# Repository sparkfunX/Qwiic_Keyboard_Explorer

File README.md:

Qwiic_Keyboard_Explorer
========================================

[*Qwiic Keyboard Explorer*](https://www.sparkfun.com/products/16184)

The Qwiic Keyboard Explorer is a 14-key mechanical keyboard kit based on our Qwiic Pro Micro development board. On its own, it makes a conveniently sized programmable macro pad, but we've also included plenty of prototyping space along the top for experimenting with all kinds of keyboard peripherals. If soldering isn't your thing, take advantage of the Pro Micro's Qwiic connector to attach any board from our Qwiic ecosystem! The standoff holes surrounding the prototyping area are spaced to accommodate most Qwiic boards for convenient mounting.

SparkFun labored with love to design this board. Feel like supporting open source hardware? 
Buy a [board](https://www.sparkfun.com/products/16184) from SparkFun!

Repository Contents
-------------------

* **/Hardware** - Eagle design files (.brd, .sch)
* **/Software** - Arduino Example Code

License Information
-------------------

This product is _**open source**_! 

Please review the LICENSE.md file for license information. 

If you have any questions or concerns on licensing, please contact technical support on our [SparkFun forums](https://forum.sparkfun.com/viewforum.php?f=152).

Distributed as-is; no warranty is given.

- Your friends at SparkFun.

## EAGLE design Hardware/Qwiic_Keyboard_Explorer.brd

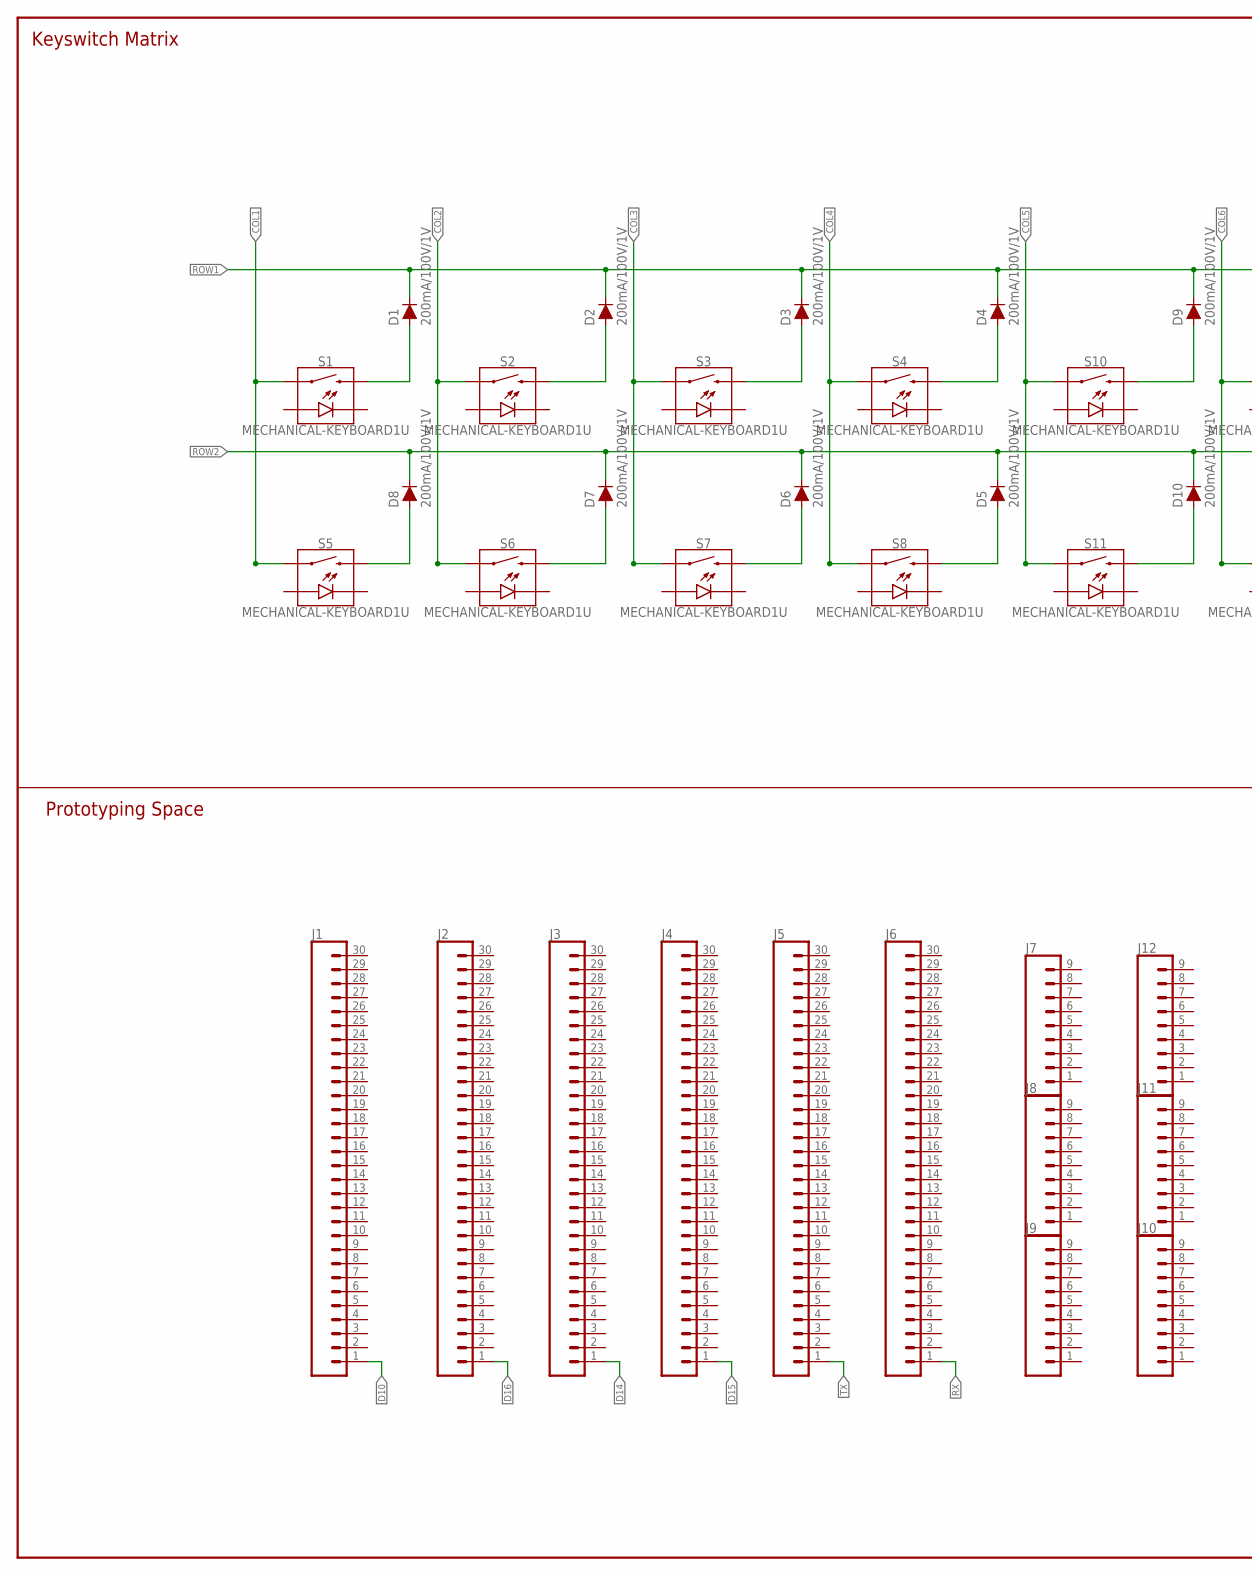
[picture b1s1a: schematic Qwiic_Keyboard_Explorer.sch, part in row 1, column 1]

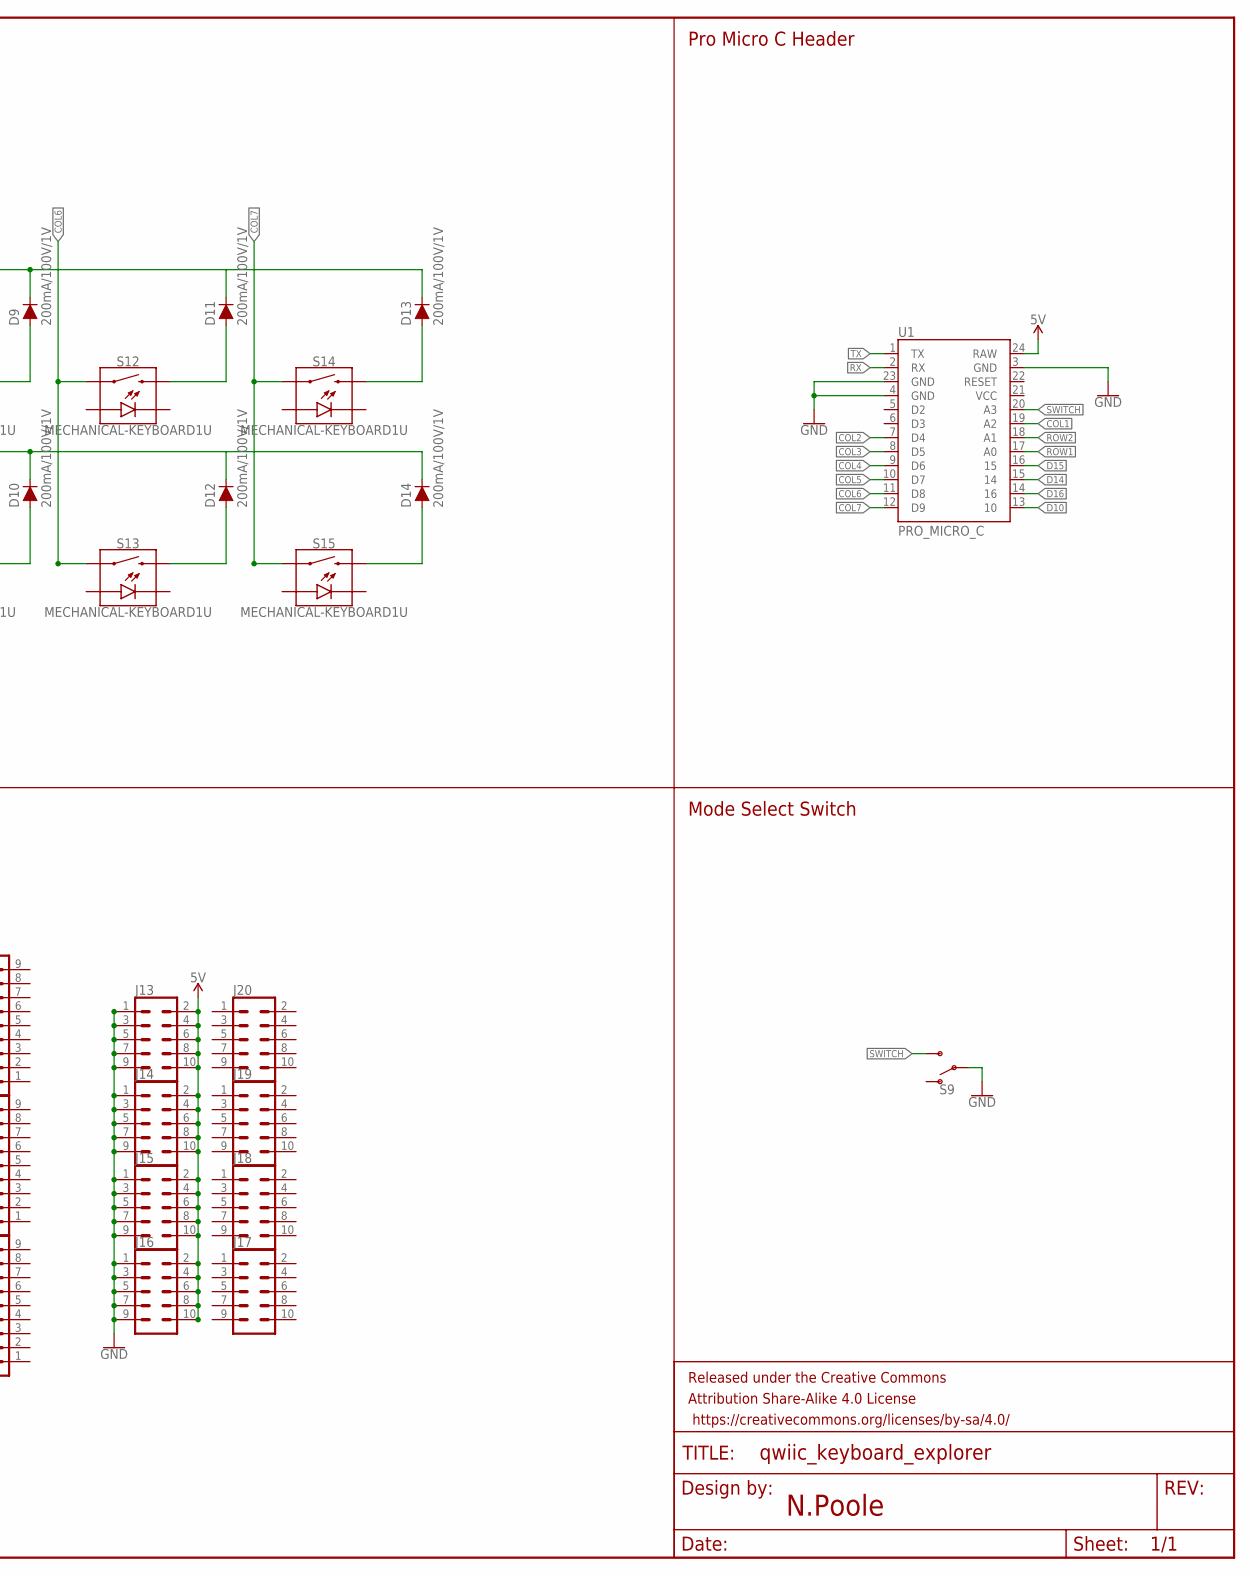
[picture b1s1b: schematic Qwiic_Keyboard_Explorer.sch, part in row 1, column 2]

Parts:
D1, D2, D3, D4, D5, D6, D7, D8, D9, D10, D11, D12, D13, D14: 200mA/100V/1V; DIODE-1N4148-KIT
FRAME1: FRAME-LEDGER; CREATIVE_COMMONS
J1, J2, J3, J4, J5, J6: CONN_30NO_SILK; 1X30_NO_SILK
J7, J8, J9, J10, J11, J12: CONN_09NO_SILK; 1X09_NO_SILK
J13, J14, J15, J16, J17, J18, J19, J20: CONN_05X2NO_SILK; 2X5_NOSILK
S1, S2, S3, S4, S5, S6, S7, S8, S10, S11, S12, S13, S14, S15: MECHANICAL-KEYBOARD1U; CHERRY-MX-LED-1U
S9: SWITCH-SPDT-PTH-11.6X4.0MM-KIT; SWITCH_SPDT_PTH_11.6X4.0MM_KIT
U1: PRO_MICRO_C

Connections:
5V: J13.2, J13.4, J13.6, J13.8, J13.10, J14.2, J14.4, J14.6, J14.8, J14.10, J15.2, J15.4, J15.6, J15.8, J15.10, J16.2, J16.4, J16.6, J16.8, J16.10, U1.24 (RAW)
COL1: S1.S1 (1), S5.S1 (1), U1.19 (A2)
COL2: S2.S1 (1), S6.S1 (1), U1.7 (D4)
COL3: S3.S1 (1), S7.S1 (1), U1.8 (D5)
COL4: S4.S1 (1), S8.S1 (1), U1.9 (D6)
COL5: S10.S1 (1), S11.S1 (1), U1.10 (D7)
COL6: S12.S1 (1), S13.S1 (1), U1.11 (D8)
COL7: S14.S1 (1), S15.S1 (1), U1.12 (D9)
D10: J1.1, U1.13 (10)
D14: J3.1, U1.15 (14)
D15: J4.1, U1.16 (15)
D16: J2.1, U1.14 (16)
GND: J13.1, J13.3, J13.5, J13.7, J13.9, J14.1, J14.3, J14.5, J14.7, J14.9, J15.1, J15.3, J15.5, J15.7, J15.9, J16.1, J16.3, J16.5, J16.7, J16.9, S9.2, U1.3 (GND), U1.4 (GND), U1.23 (GND)
unnamed: D8.A, S5.S2 (2)
unnamed: D7.A, S6.S2 (2)
unnamed: D6.A, S7.S2 (2)
unnamed: D5.A, S8.S2 (2)
unnamed: D4.A, S4.S2 (2)
unnamed: D3.A, S3.S2 (2)
unnamed: D2.A, S2.S2 (2)
unnamed: D1.A, S1.S2 (2)
unnamed: D9.A, S10.S2 (2)
unnamed: D10.A, S11.S2 (2)
unnamed: D11.A, S12.S2 (2)
unnamed: D12.A, S13.S2 (2)
unnamed: D13.A, S14.S2 (2)
unnamed: D14.A, S15.S2 (2)
ROW1: D1.C, D2.C, D3.C, D4.C, D9.C, D11.C, D13.C, U1.17 (A0)
ROW2: D5.C, D6.C, D7.C, D8.C, D10.C, D12.C, D14.C, U1.18 (A1)
RX: J6.1, U1.2 (RX)
SWITCH: S9.3 (S), U1.20 (A3)
TX: J5.1, U1.1 (TX)

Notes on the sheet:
Keyswitch Matrix
Prototyping Space
Pro Micro C Header
Mode Select Switch
N.Poole

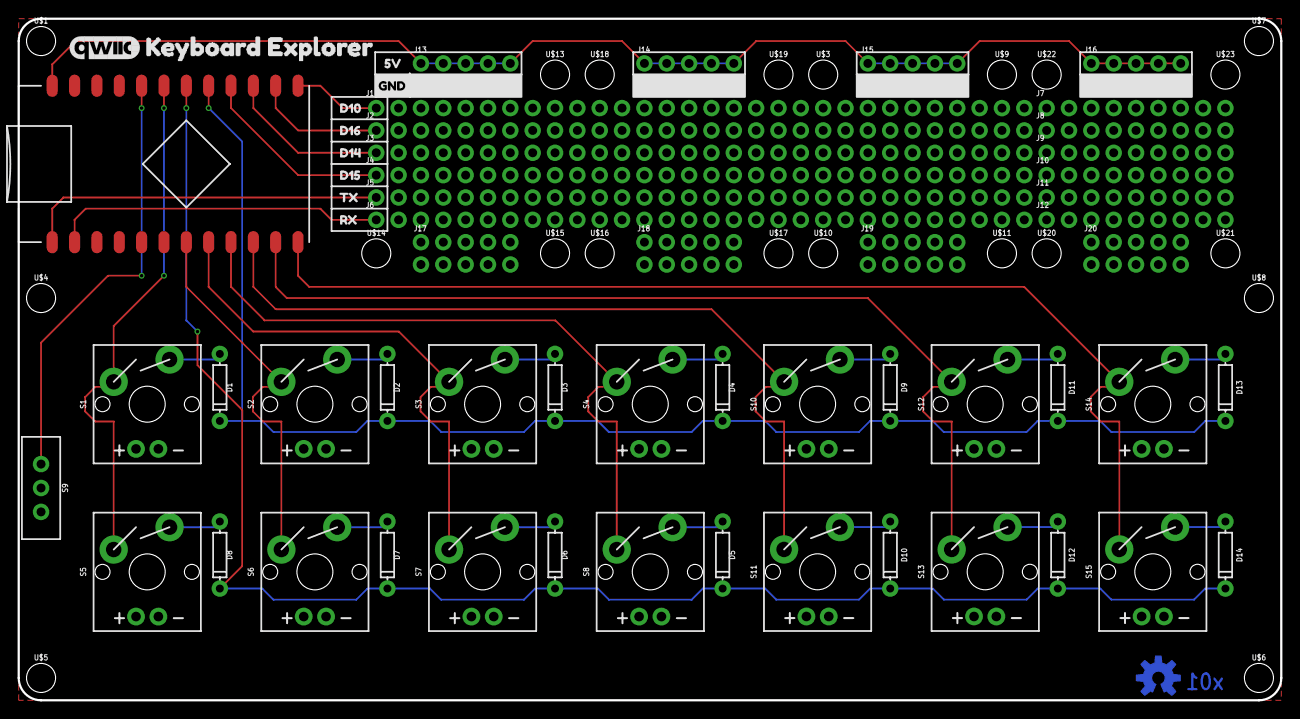
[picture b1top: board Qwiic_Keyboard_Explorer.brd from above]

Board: 2 copper layers, 143.5 x 77.5 mm, 83 parts (1 on the bottom side), 32 nets.

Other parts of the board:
U$1, U$3, U$4, U$5, U$6, U$7, U$8, U$9, U$10, U$11, U$13, U$14, U$15, U$16, U$17, U$18, U$19, U$20, U$21, U$22, U$23: STAND-OFF
U$2: KEYBOARD_EXPLORER0
U$12: 5V0
U$24: QWIIC_8MM
U$25: GND-04
U$26: D101
U$27: D162
U$28: D143
U$29: D154
U$30: TX5
U$31: RX6
U$32: OSHW-LOGO-M_COPPER

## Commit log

2019-12-19 Routing Continues
2019-12-19 Proto x01
2019-12-19 Add gitignore remove backup files
    housecleaning
2020-08-13 Example Code
2020-08-13 Aesthetic tweaks to eagle files
2020-11-20 Create License.md
    Added license

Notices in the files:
parts and their libraries:
SparkFun-Boards: Licensing: Creative Commons ShareAlike 4.0 International - https://creativecommons.org/licenses/by-sa/4.0
SparkFun-Aesthetics: Released under the Creative Commons Attribution Share-Alike 4.0 License
SparkFun-Aesthetics: https://creativecommons.org/licenses/by-sa/4.0
